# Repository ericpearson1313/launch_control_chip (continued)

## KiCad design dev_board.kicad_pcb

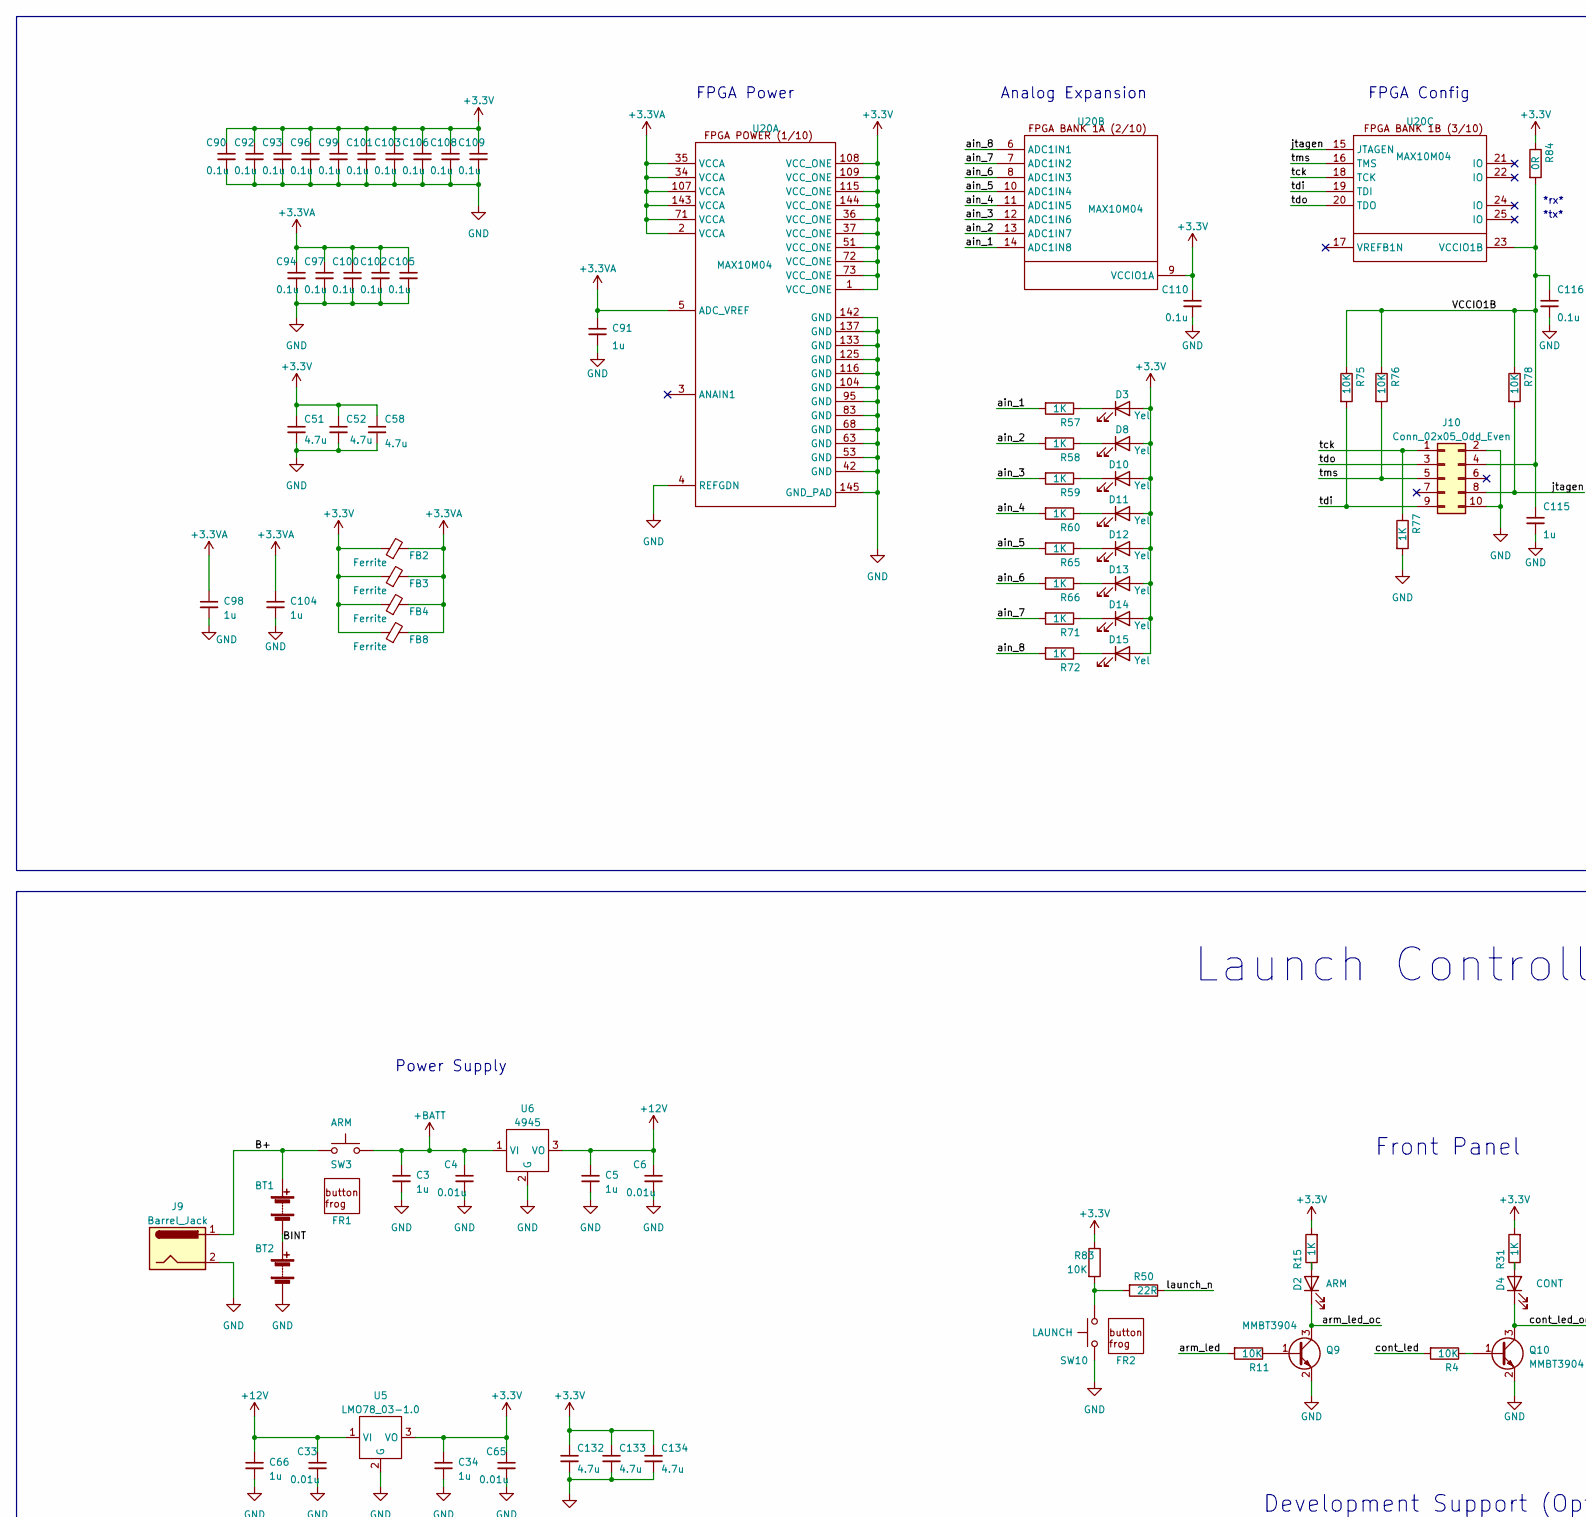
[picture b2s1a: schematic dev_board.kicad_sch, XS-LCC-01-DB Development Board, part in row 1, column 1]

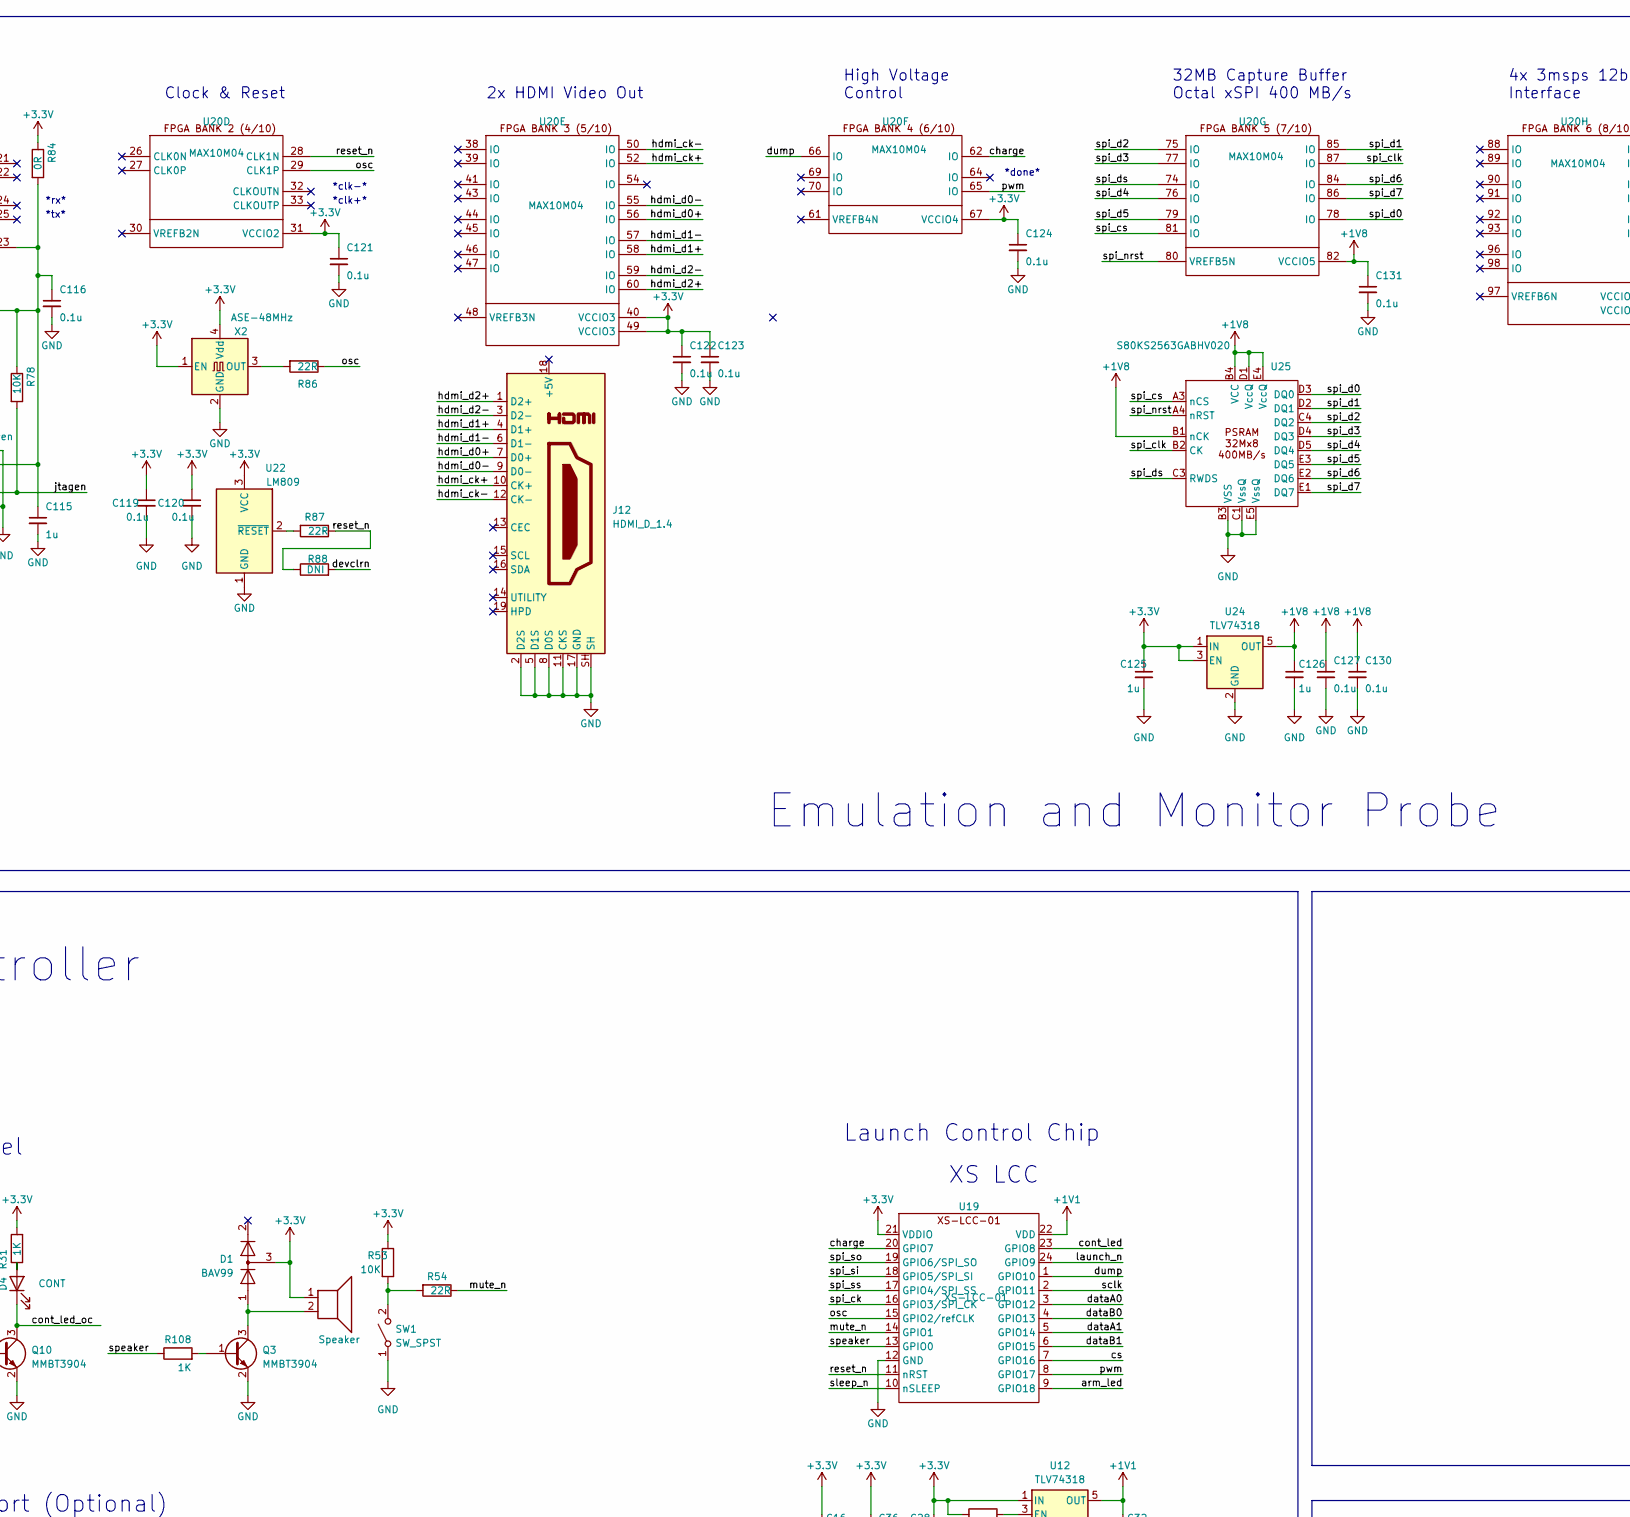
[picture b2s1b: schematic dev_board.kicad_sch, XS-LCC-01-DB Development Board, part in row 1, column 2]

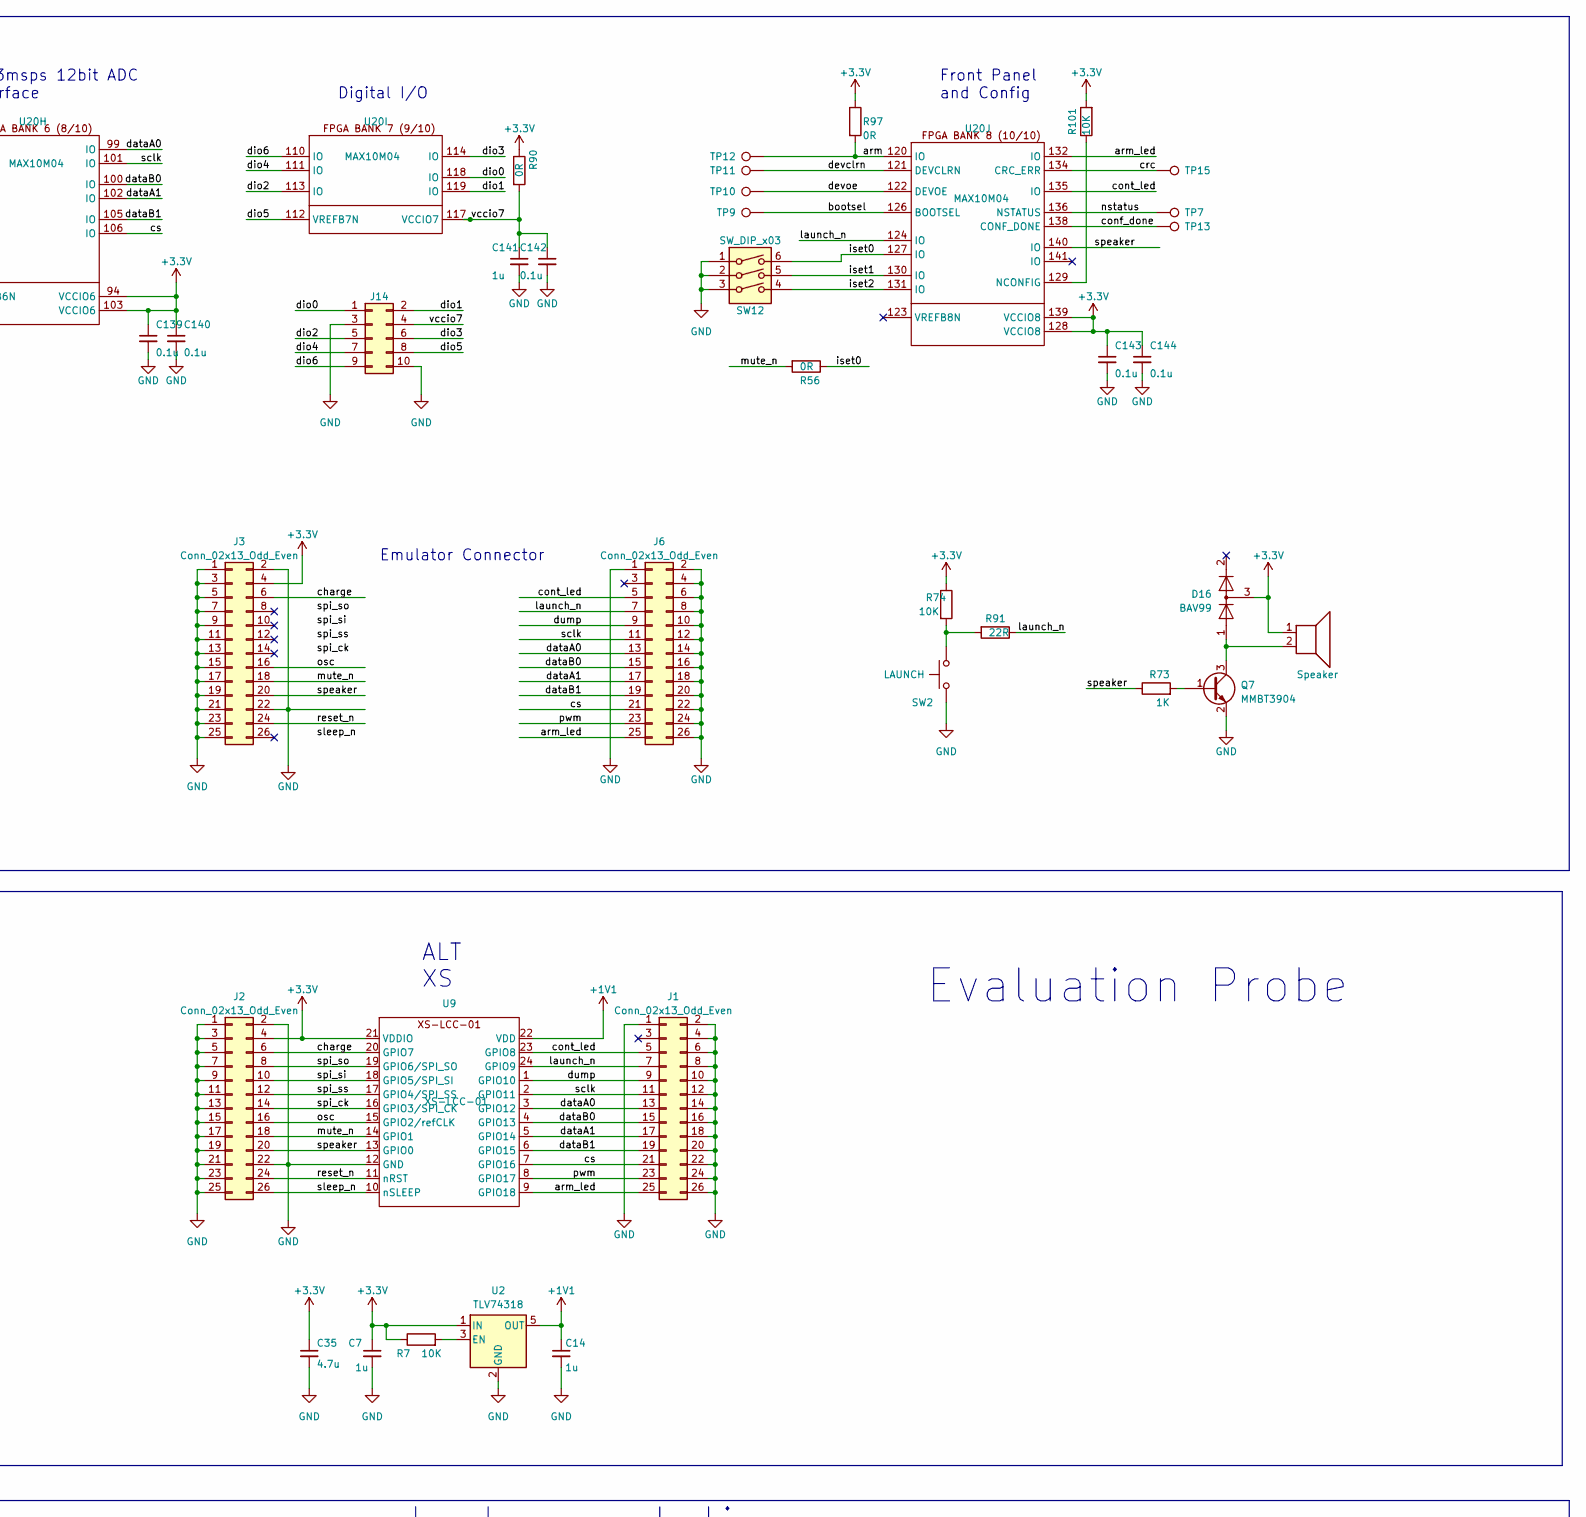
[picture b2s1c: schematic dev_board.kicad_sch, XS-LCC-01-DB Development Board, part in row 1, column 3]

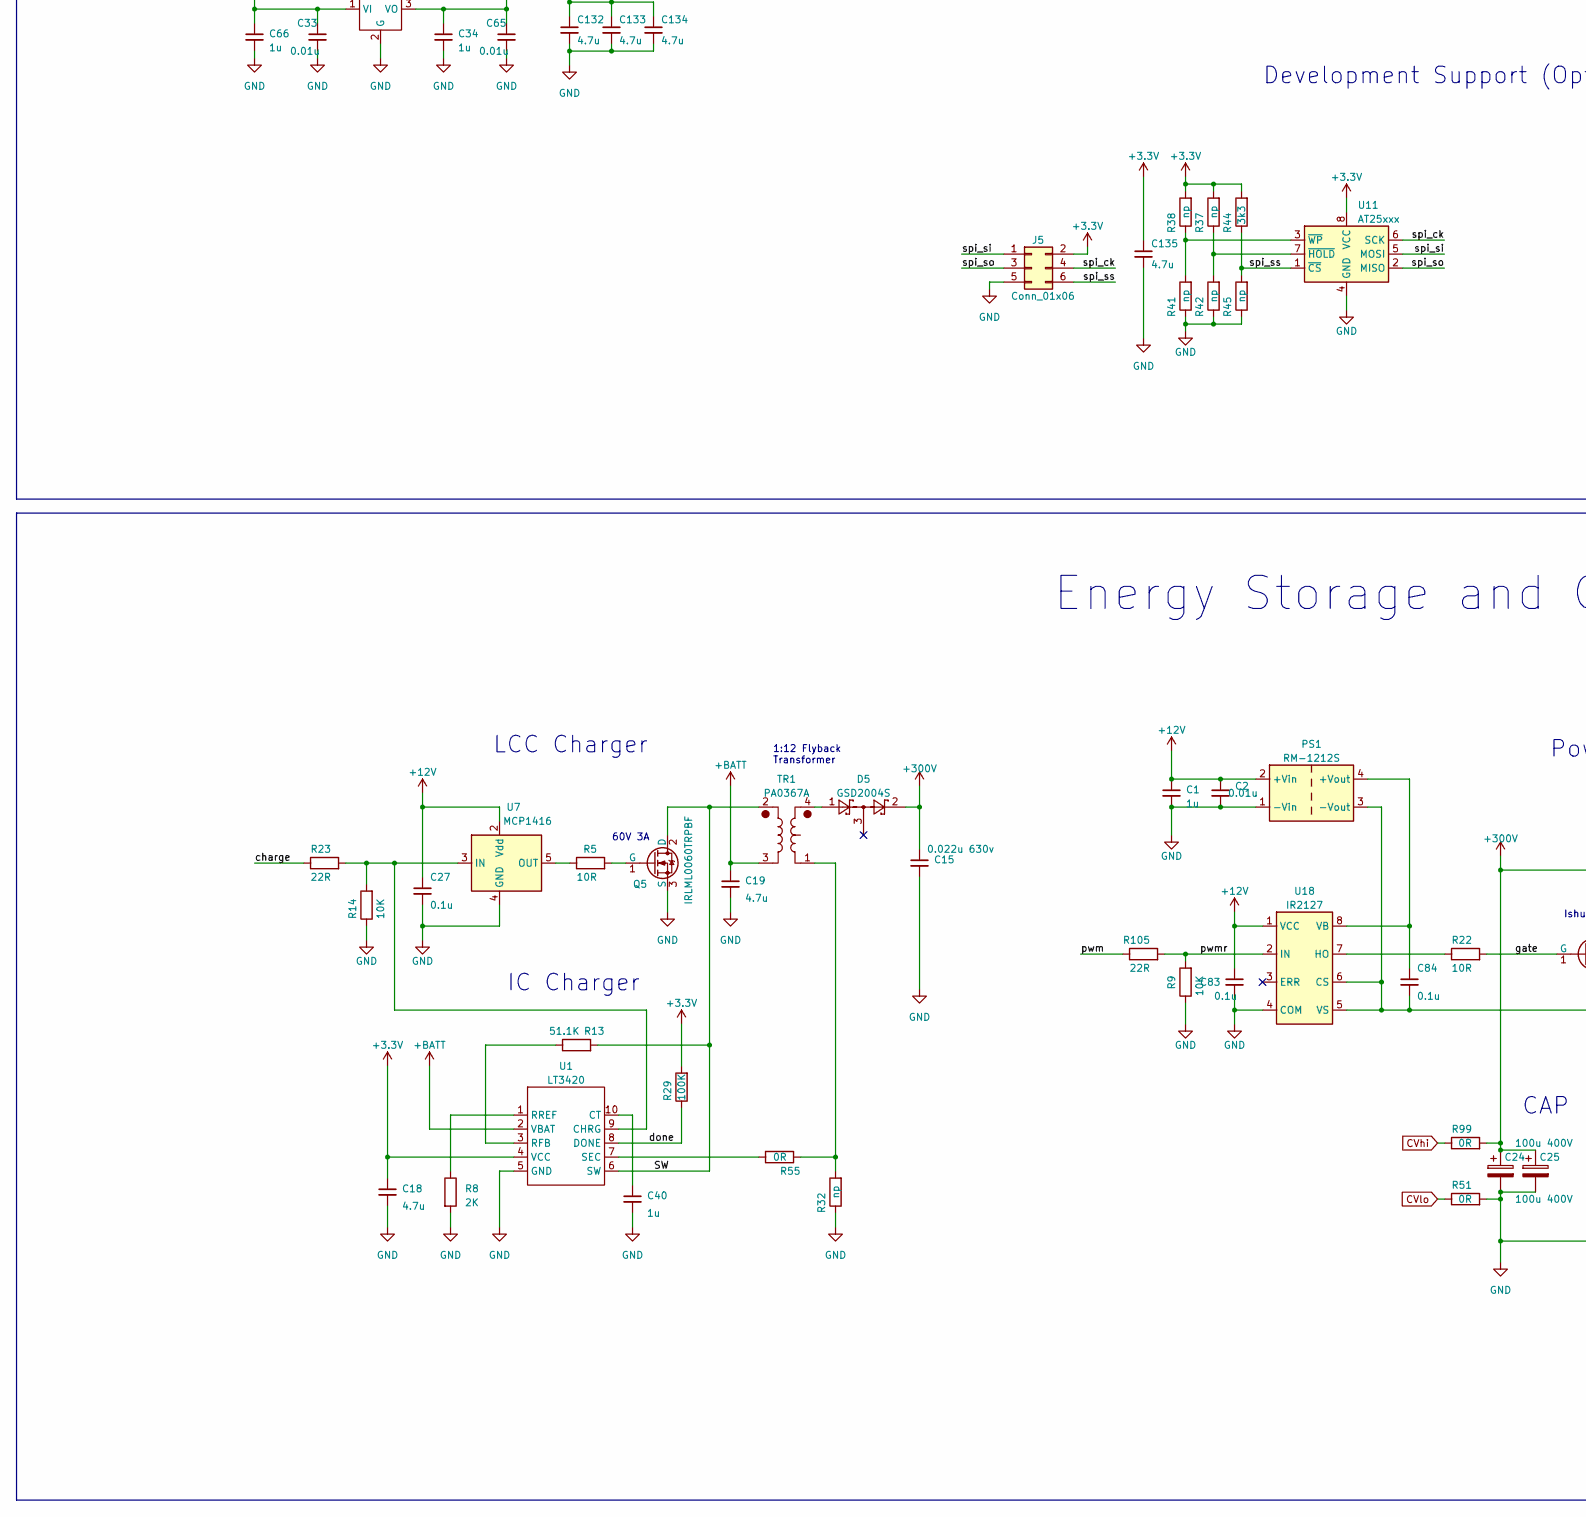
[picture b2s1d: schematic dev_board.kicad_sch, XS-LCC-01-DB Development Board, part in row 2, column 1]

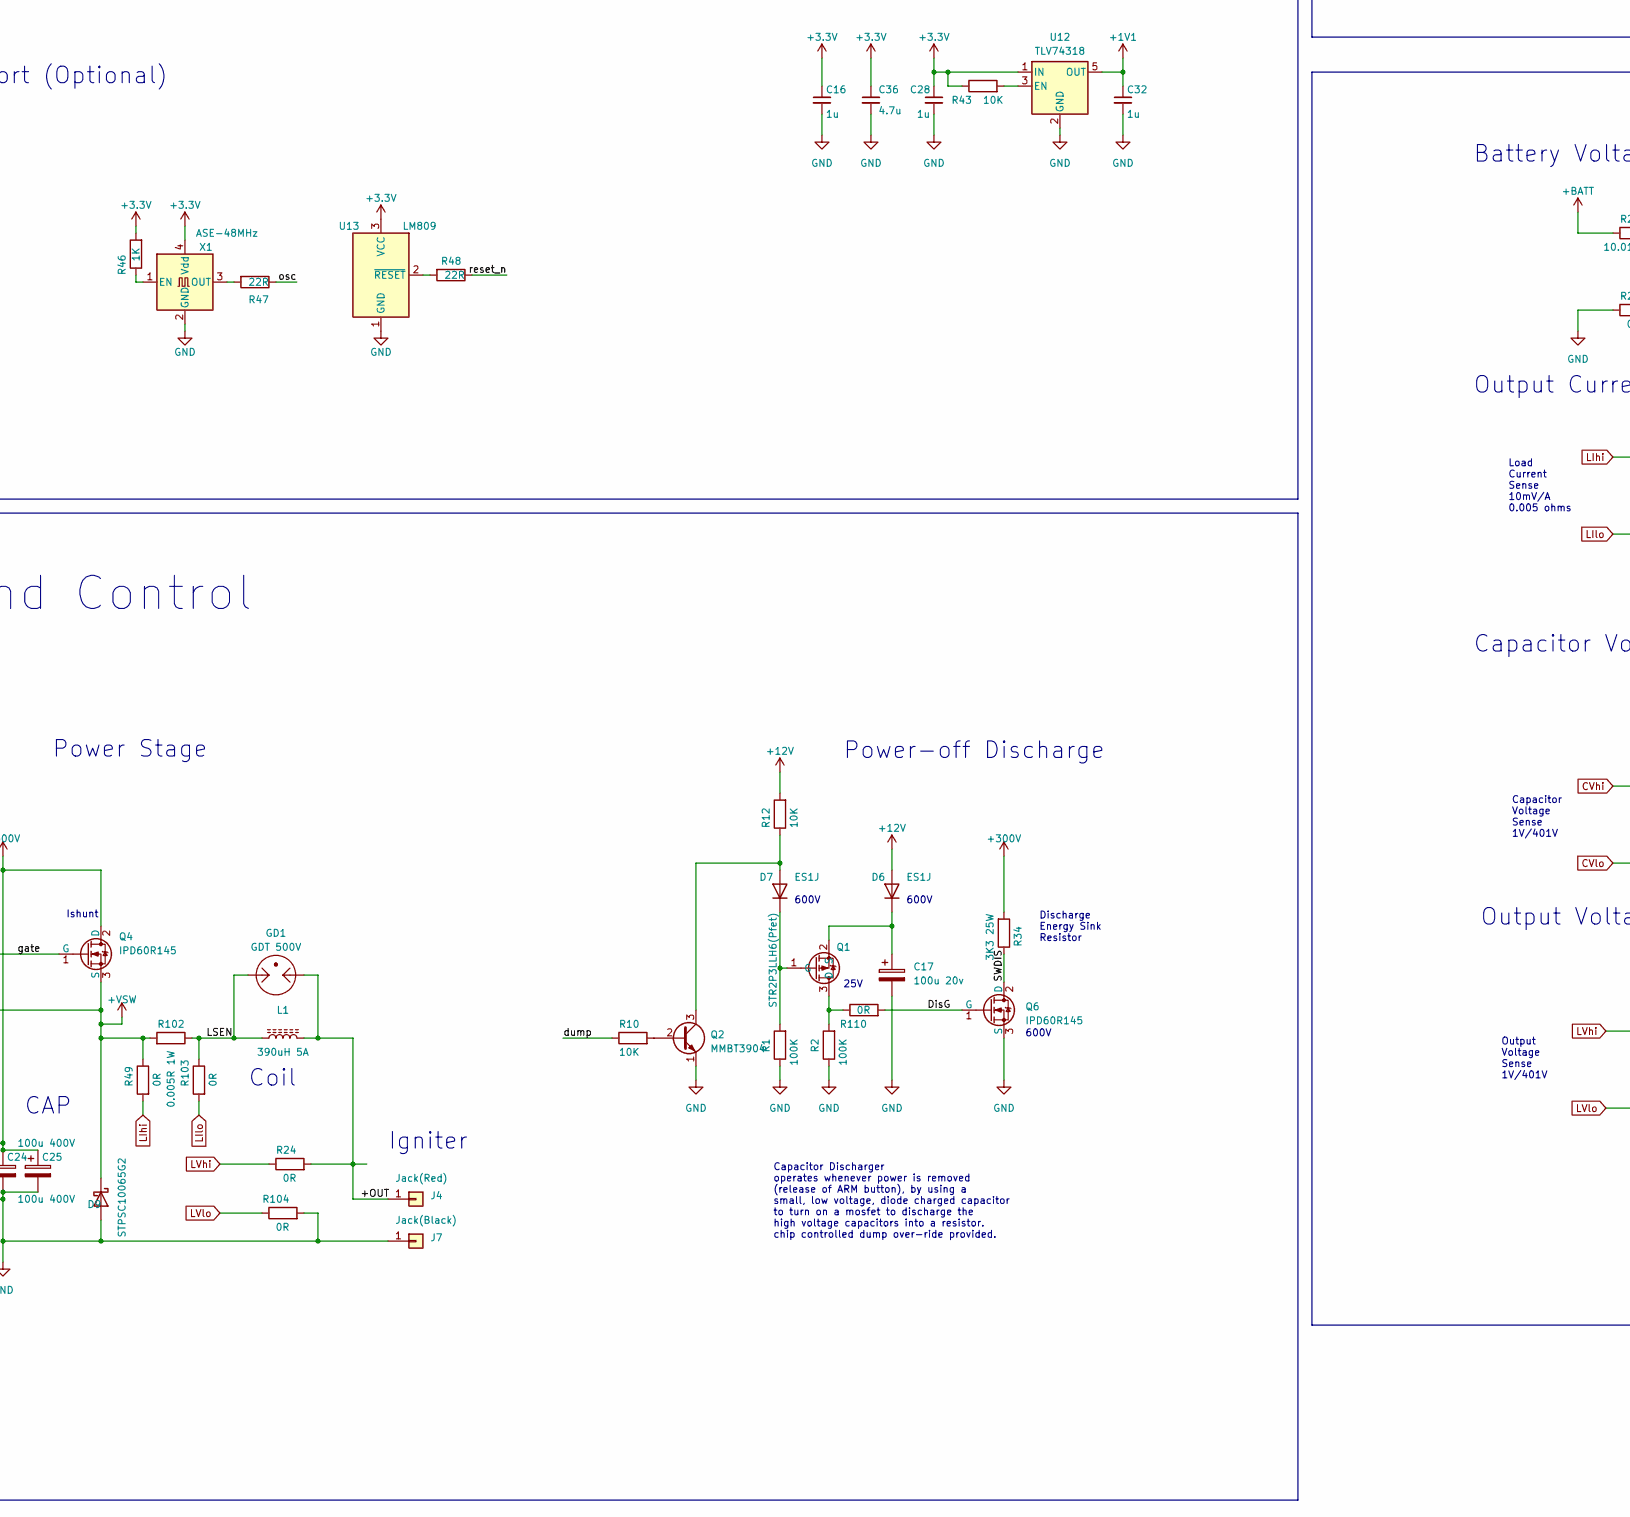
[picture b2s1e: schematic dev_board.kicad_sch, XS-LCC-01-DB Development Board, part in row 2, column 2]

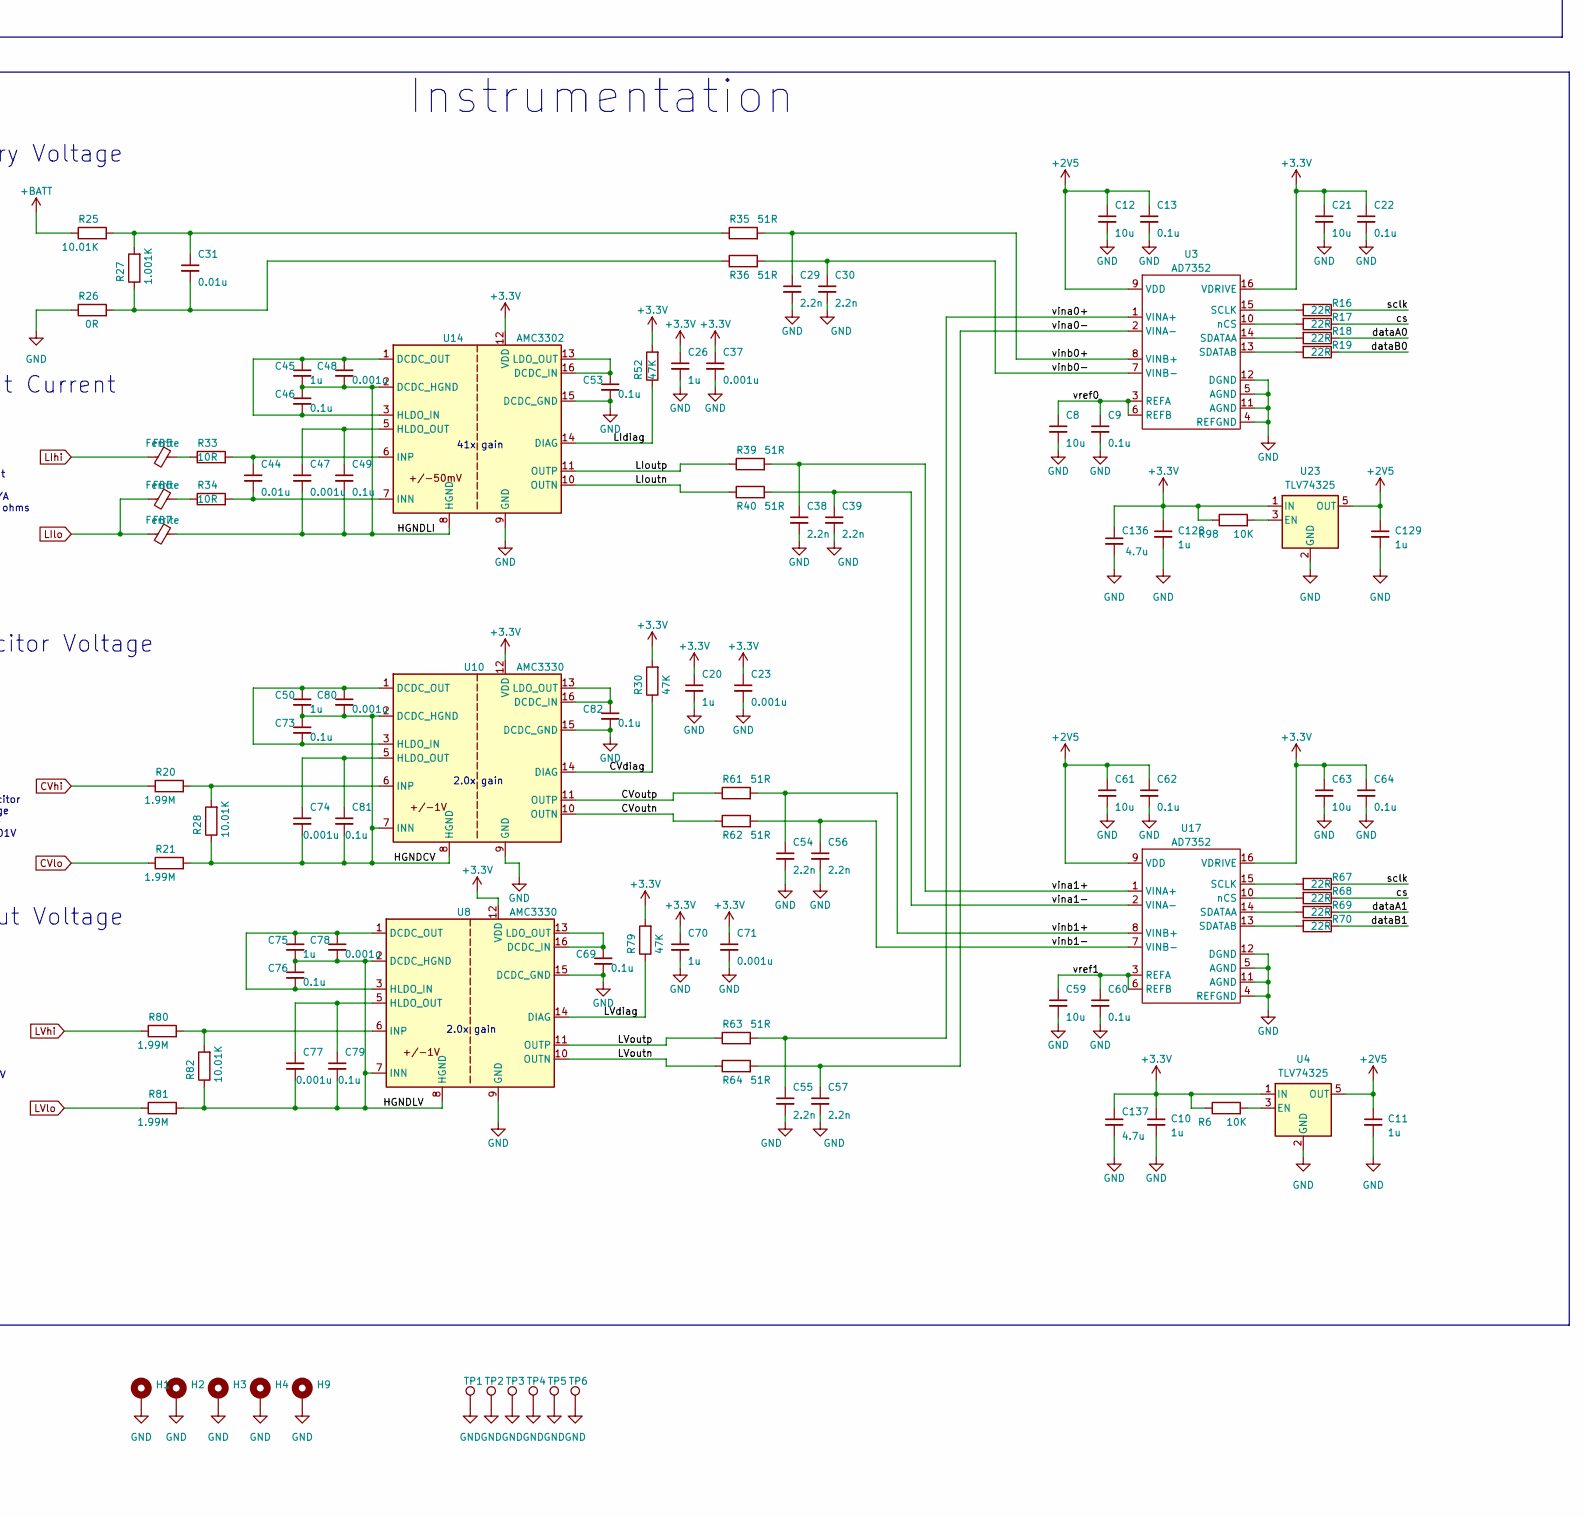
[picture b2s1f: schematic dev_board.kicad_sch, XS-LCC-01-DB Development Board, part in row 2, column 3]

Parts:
BT1, BT2: BatteryHolder_Keystone_2462_2xAA
C1, C3, C5, C7, C10, C11, C14, C16, C20, C26, C28, C32, C34, C40, C45, C50, C66, C70, C75, C91, C98, C104, C115, C125, C126, C128, C129, C141: 1u; C_0603_1608Metric
C2, C4, C6, C31, C33, C44, C65: 0.01u; C_0603_1608Metric
C8, C12, C21, C59, C61, C63: 10u; C_1206_3216Metric
C9, C13, C22, C27, C46, C49, C53, C60, C62, C64, C69, C73, C76, C79, C81, C82, C83, C84, C90, C92, C93, C94, C96, C97, C99, C100, C101, C102, C103, C105, C106, C108, C109, C110, C116, C119, C120, C121, C122, C123, C124, C127, C130, C131, C139, C140, C142, C143, C144: 0.1u; C_0603_1608Metric
C15: 0.022u 630v; C_1206_3216Metric
C17: 100u 20v; C_Radial_D5.0mm_H7.0mm_P2.00mm
C18, C19, C35, C36, C51, C52, C58, C132, C133, C134, C135, C136, C137: 4.7u; C_1206_3216Metric
C23, C37, C47, C48, C71, C74, C77, C78, C80: 0.001u; C_0603_1608Metric
C24, C25: 100u 400V; CP_Radial_D16.0mm_P7.50mm
C29, C30, C38, C39, C54, C55, C56, C57: 2.2n; C_0603_1608Metric
D1, D16: BAV99; SOT-23
D2: ARM; LED_0603_1608Metric
D3, D8, D10, D11, D12, D13, D14, D15: Yel; LED_0603_1608Metric
D4: CONT; LED_0603_1608Metric
D5: GSD2004S; SOT-23; JLC C85606
D6, D7: ES1J; D_SMA; JLC C99410
D9: ‎STPSC10065G2; TO-263-2_TabPin1; JLC C602663
FB2, FB3, FB4, FB5, FB6, FB7, FB8: Ferrite; L_0603_1608Metric
FR1, FR2: button_frog
GD1: GDT 500V; C_1812_4532Metric_Pad1.57x3.40mm_HandSolder
H1, H2, H3, H4, H9: MountingHole_3mm_Pad
J1, J2, J3, J6: Conn_02x13_Odd_Even; PinSocket_2x13_P2.54mm_Vertical
J4: Jack(Red); CalTest_CT3151
J5: Conn_01x06; PinHeader_2x03_P2.54mm_Vertical
J7: Jack(Black); CalTest_CT3151
J9: Barrel_Jack; BarrelJack_CUI_PJ-063AH_Horizontal
J10, J14: Conn_02x05_Odd_Even; PinHeader_2x05_P2.54mm_Vertical
J12: HDMI_D_1.4; HDMI_A_Amphenol_10029449-x01xLF_Horizontal
L1: 390uH 5A; L_Toroid_Vertical_L35.6mm_W17.8mm_P12.70mm_Pulse_E
LS1, LS2: Speaker; PUIAudio_SMT_0825_S_4_R
PS1: RM-1212S; Converter_DCDC_Murata_MEE1SxxxxSC_THT
Q1: STR2P3LLH6(Pfet); SOT-23
Q2, Q3, Q7, Q9, Q10: MMBT3904; SOT-23
Q4, Q6: IPD60R145; TO-252-2; JLC C3277918
Q5: IRLML0060TRPBF; SOT-23; JLC C3277918
R1, R2, R29: 100K; R_0603_1608Metric; JLC C319967
R4, R11, R75, R76, R78, R101: 10K; R_0603_1608Metric; JLC C319967
R5, R22, R33, R34: 10R; R_0603_1608Metric; JLC C778416
R6, R7, R43, R98: 10K; R_0603_1608Metric; JLC C778416
R8: 2K; R_0603_1608Metric; JLC C319700
R9, R12, R14, R53, R74, R83: 10K; R_0603_1608Metric; JLC C491211
R10: 10K; R_0603_1608Metric
R13: 51.1K; R_0603_1608Metric; JLC C234563
R15, R31, R46, R57, R58, R59, R60, R65, R66, R71, R72, R73, R77, R108: 1K; R_0603_1608Metric; JLC C319967
R16, R17, R18, R19, R47, R48, R50, R54, R67, R68, R69, R70, R86, R87, R91: 22R; R_0603_1608Metric; JLC C319967
R20, R21, R80, R81: 1.99M; R_0603_1608Metric; JLC C778416
R23, R105: 22R; R_0603_1608Metric; JLC C778416
R24, R26, R49, R51, R56, R99, R103, R104: 0R; R_0603_1608Metric; JLC C778416
R25, R28, R82: 10.01K; R_0603_1608Metric; JLC C778416
R27: 1.001K; R_0603_1608Metric; JLC C778416
R30, R52, R79: 47K; R_0603_1608Metric; JLC C778416
R32, R37, R38, R41, R42, R45: np; R_0603_1608Metric
R35, R36, R39, R40, R61, R62, R63, R64: 51R; R_0603_1608Metric; JLC C778416
R44: 3k3; R_0603_1608Metric; JLC C319967
R55, R84, R90, R110: 0R; R_0603_1608Metric; JLC C319967
R88: DNI; R_0603_1608Metric; JLC C491211
R97: 0R; R_0603_1608Metric; JLC C491211
R102: 0.005R 1W; R_2818 current sense
SW1: SW_SPST; SW_E-Switch_EG1224_SPDT_Angled
SW2, SW10: LAUNCH; SW_SPST_HP03
SW3: ARM; SW_SPST_HP03
SW12: SW_DIP_x03; SW_DIP_SPSTx03_Slide_Omron_A6S-310x_W8.9mm_P2.54mm
TP1, TP2, TP3, TP4, TP5, TP6: TestPoint_Keystone_5000-5004_Miniature
TP7, TP13: TestPoint_Pad_D1.0mm
TP9, TP10, TP11, TP12, TP15: TestPoint_Pad_D1.5mm
TR1: PA0367A; PA0637A Pulse Coil 3D; JLC C5382098
U1: LT3420; MSOP-10_3x3mm_P0.5mm; JLC C670531
U2, U12, U24: TLV74318; SOT-23-5
U3, U17: AD7352; TSSOP-16_4.4x5mm_P0.65mm
U4, U23: TLV74325; SOT-23-5
U5: LMO78_03-1.0; Converter_DCDC_Murata_OKI-78SR_Horizontal
U6: 4945; Converter_DCDC_Murata_OKI-78SR_Horizontal
U7: MCP1416; SOT-23-5
U8, U10: AMC3330; SOIC-16W_7.5x10.3mm_P1.27mm
U9, U19: XS-LCC-01; QFN-24-3x3mm
U11: AT25xxx; SOIC-8_3.9x4.9mm_P1.27mm
U13, U22: LM809; SOT-23
U14: AMC3302; SOIC-16W_7.5x10.3mm_P1.27mm
U18: IR2127; SOIC-8_3.9x4.9mm_P1.27mm; JLC C356723
U20: MAX10M04; EQFP-144-1EP_20x20mm_P0.5mm_EP8.93x8.7mm_ThermalVias
U25: S80KS2563GABHV020; FBGA-24_6mmx8mm_Layout5x5_P1.00mm
X1, X2: ASE-48MHz; Oscillator_SMD_Abracon_ASV-4Pin_7.0x5.1mm_HandSoldering

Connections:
+1V1: C14.1, C32.1, U2.5 (OUT), U9.22 (VDD), U12.5 (OUT), U19.22 (VDD)
+1V8: C126.1, C127.1, C130.1, C131.1, U20.82 (VCCIO5), U24.5 (OUT), U25.B1 (nCK), U25.B4 (VCC), U25.D1 (VccQ), U25.E4 (VccQ)
+2V5: C11.1, C12.1, C13.1, C61.1, C62.1, C129.1, U3.9 (VDD), U4.5 (OUT), U17.9 (VDD), U23.5 (OUT)
+3.3V: C7.1, C10.1, C16.1, C18.1, C20.1, C21.1, C22.1, C23.1, C26.1, C28.1, C34.1, C35.1, C36.1, C37.1, C51.1, C52.1, C58.1, C63.1, C64.1, C65.1, C70.1, C71.1, C90.1, C92.1, C93.1, C96.1, C99.1, C101.1, C103.1, C106.1, C108.1, C109.1, C110.1, C119.1, C120.1, C121.1, C122.1, C123.1, C124.1, C125.1, C128.1, C132.1, C133.1, C134.1, C135.1, C136.1, C137.1, C139.1, C140.1, C143.1, C144.1, D1.3 (K), D3.2 (A), D8.2 (A), D10.2 (A), D11.2 (A), D12.2 (A), D13.2 (A), D14.2 (A), D15.2 (A), D16.3 (K), FB2.1, FB3.1, FB4.1, FB8.1, J2.4, J3.4, J5.2, LS1.1, LS2.1, R6.1, R7.1, R15.2, R29.2, R30.2, R31.2, R37.2, R38.2, R43.1, R44.2, R46.2, R52.2, R53.1, R74.1, R79.2, R83.1, R84.1, R90.1, R97.1, R98.1, R101.2, U1.4 (VCC), U2.1 (IN), U3.16 (VDRIVE), U4.1 (IN), U5.3 (VO), U8.12 (VDD), U9.21 (VDDIO), U10.12 (VDD), U11.8 (VCC), U12.1 (IN), U13.3 (VCC), U14.12 (VDD), U17.16 (VDRIVE), U19.21 (VDDIO), U20.1 (VCC_ONE), U20.9 (VCCIO1A), U20.31 (VCCIO2), U20.36 (VCC_ONE), U20.37 (VCC_ONE), U20.40 (VCCIO3), U20.49 (VCCIO3), U20.51 (VCC_ONE), U20.67 (VCCIO4), U20.72 (VCC_ONE), U20.73 (VCC_ONE), U20.94 (VCCIO6), U20.103 (VCCIO6), U20.108 (VCC_ONE), U20.109 (VCC_ONE), U20.115 (VCC_ONE), U20.128 (VCCIO8), U20.139 (VCCIO8), U20.144 (VCC_ONE), U22.3 (VCC), U23.1 (IN), U24.1 (IN), U24.3 (EN), X1.4 (Vdd), X2.1 (EN), X2.4 (Vdd)
+3.3VA: C91.1, C94.1, C97.1, C98.1, C100.1, C102.1, C104.1, C105.1, FB2.2, FB3.2, FB4.2, FB8.2, U20.2 (VCCA), U20.5 (ADC_VREF), U20.34 (VCCA), U20.35 (VCCA), U20.71 (VCCA), U20.107 (VCCA), U20.143 (VCCA)
+12V: C1.1, C2.1, C5.1, C6.1, C27.1, C33.1, C66.1, C83.1, D6.2 (A), PS1.2 (+Vin), R12.2, U5.1 (VI), U6.3 (VO), U7.2 (Vdd), U18.1 (VCC)
+BATT: C3.1, C4.1, C19.1, R25.1, SW3.2, TR1.3, U1.2 (VBAT), U6.1 (VI)
+VSW: C84.2, D9.1 (K), PS1.3 (-Vout), Q4.3 (S), R49.1, R102.2, U18.5 (VS), U18.6 (CS)
/+OUT: GD1.1, J4.1, L1.2, R24.2
/B+: BT1.1 (+), J9.1, SW3.1
/BINT: BT1.2 (-), BT2.1 (+)
/CVdiag: R30.1, U10.14 (DIAG)
/CVoutn: R62.1, U10.10 (OUTN)
/CVoutp: R61.1, U10.11 (OUTP)
/DisG: Q6.1 (G), R110.2
/HGNDCV: C50.2, C73.1, C74.2, C80.2, C81.2, R21.2, R28.1, U10.2 (DCDC_HGND), U10.7 (INN), U10.8 (HGND)
/HGNDLI: C45.2, C46.1, C47.2, C48.2, C49.2, FB7.1, U14.2 (DCDC_HGND), U14.8 (HGND)
/HGNDLV: C75.2, C76.1, C77.2, C78.2, C79.2, R81.2, R82.1, U8.2 (DCDC_HGND), U8.7 (INN), U8.8 (HGND)
/LIdiag: R52.1, U14.14 (DIAG)
/LIoutn: R40.1, U14.10 (OUTN)
/LIoutp: R39.1, U14.11 (OUTP)
/LSEN: GD1.3, L1.1, R102.1, R103.1
/LVdiag: R79.1, U8.14 (DIAG)
/LVoutn: R64.1, U8.10 (OUTN)
/LVoutp: R63.1, U8.11 (OUTP)
/SW: Q5.2 (D), R13.2, TR1.2, U1.6 (SW)
/VCCIO1B: C115.1, C116.1, J10.4, R75.1, R76.1, R78.1, R84.2, U20.23 (VCCIO1B)
/ain_1: R57.2, U20.14 (ADC1IN8)
/ain_2: R58.2, U20.13 (ADC1IN7)
/ain_3: R59.2, U20.12 (ADC1IN6)
/ain_4: R60.2, U20.11 (ADC1IN5)
/ain_5: R65.2, U20.10 (ADC1IN4)
/ain_6: R66.2, U20.8 (ADC1IN3)
/ain_7: R71.2, U20.7 (ADC1IN2)
/ain_8: R72.2, U20.6 (ADC1IN1)
/arm: R97.2, TP12.1, U20.120 (IO)
/arm_led: J1.25, J6.25, R11.2, U9.9 (GPIO18), U19.9 (GPIO18), U20.132 (IO)
/arm_led_oc: D2.1 (K), Q9.3 (C)
/bootsel: TP9.1, U20.126 (BOOTSEL)
/charge: J2.6, J3.6, R23.1, U9.20 (GPIO7), U19.20 (GPIO7), U20.62 (IO)
/conf_done: TP13.1, U20.138 (CONF_DONE)
/cont_led: J1.5, J6.5, R4.2, U9.23 (GPIO8), U19.23 (GPIO8), U20.135 (IO)
/cont_led_oc: D4.1 (K), Q10.3 (C)
/crc: TP15.1, U20.134 (CRC_ERR)
/cs: J1.21, J6.21, R17.1, R68.1, U9.7 (GPIO16), U19.7 (GPIO16), U20.106 (IO)
/dataA0: J1.13, J6.13, R18.1, U9.3 (GPIO12), U19.3 (GPIO12), U20.99 (IO)
/dataA1: J1.17, J6.17, R69.1, U9.5 (GPIO14), U19.5 (GPIO14), U20.102 (IO)
/dataB0: J1.15, J6.15, R19.1, U9.4 (GPIO13), U19.4 (GPIO13), U20.100 (IO)
/dataB1: J1.19, J6.19, R70.1, U9.6 (GPIO15), U19.6 (GPIO15), U20.105 (IO)
/devclrn: R88.2, TP11.1, U20.121 (DEVCLRN)
/devoe: TP10.1, U20.122 (DEVOE)
/dio0: J14.1, U20.118 (IO)
/dio1: J14.2, U20.119 (IO)
/dio2: J14.5, U20.113 (IO)
/dio3: J14.6, U20.114 (IO)
/dio4: J14.7, U20.111 (IO)
/dio5: J14.8, U20.112 (VREFB7N)
/dio6: J14.9, U20.110 (IO)
/done: R29.1, U1.8 (DONE)
/dump: J1.9, J6.9, R10.1, U9.1 (GPIO10), U19.1 (GPIO10), U20.66 (IO)
/gate: Q4.1 (G), R22.2
/hdmi_ck+: J12.10 (CK+), U20.52 (IO)
/hdmi_ck-: J12.12 (CK-), U20.50 (IO)
/hdmi_d0+: J12.7 (D0+), U20.56 (IO)
/hdmi_d0-: J12.9 (D0-), U20.55 (IO)
/hdmi_d1+: J12.4 (D1+), U20.58 (IO)
/hdmi_d1-: J12.6 (D1-), U20.57 (IO)
/hdmi_d2+: J12.1 (D2+), U20.60 (IO)
/hdmi_d2-: J12.3 (D2-), U20.59 (IO)
/iset0: R56.1, SW12.6, U20.127 (IO)
/iset1: SW12.5, U20.130 (IO)
/iset2: SW12.4, U20.131 (IO)
/jtagen: J10.8, R78.2, U20.15 (JTAGEN)
/launch_n: J1.7, J6.7, R50.1, R91.1, U9.24 (GPIO9), U19.24 (GPIO9), U20.124 (IO)
/mute_n: J2.18, J3.18, R54.1, R56.2, U9.14 (GPIO1), U19.14 (GPIO1)
/nstatus: TP7.1, U20.136 (NSTATUS)
/osc: J2.16, J3.16, R47.1, R86.1, U9.15 (GPIO2/refCLK), U19.15 (GPIO2/refCLK), U20.29 (CLK1P)
/pwm: J1.23, J6.23, R105.1, U9.8 (GPIO17), U19.8 (GPIO17), U20.65 (IO)
/pwmr: R9.2, R105.2, U18.2 (IN)
/reset_n: J2.24, J3.24, R48.1, R87.1, R88.1, U9.11 (nRST), U19.11 (nRST), U20.28 (CLK1N)
/sclk: J1.11, J6.11, R16.1, R67.1, U9.2 (GPIO11), U19.2 (GPIO11), U20.101 (IO)
/sleep_n: J2.26, U9.10 (nSLEEP), U19.10 (nSLEEP)
/speaker: J2.20, J3.20, R73.1, R108.1, U9.13 (GPIO0), U19.13 (GPIO0), U20.140 (IO)
/spi_ck: J2.14, J5.4, U9.16 (GPIO3/SPI_CK), U11.6 (SCK), U19.16 (GPIO3/SPI_CK)
/spi_clk: U20.87 (IO), U25.B2 (CK)
/spi_cs: U20.81 (IO), U25.A3 (nCS)
/spi_d0: U20.78 (IO), U25.D3 (DQ0)
/spi_d1: U20.85 (IO), U25.D2 (DQ1)
/spi_d2: U20.75 (IO), U25.C4 (DQ2)
/spi_d3: U20.77 (IO), U25.D4 (DQ3)
/spi_d4: U20.76 (IO), U25.D5 (DQ4)
/spi_d5: U20.79 (IO), U25.E3 (DQ5)
/spi_d6: U20.84 (IO), U25.E2 (DQ6)
/spi_d7: U20.86 (IO), U25.E1 (DQ7)
/spi_ds: U20.74 (IO), U25.C3 (RWDS)
/spi_nrst: U20.80 (VREFB5N), U25.A4 (nRST)
/spi_si: J2.10, J5.1, U9.18 (GPIO5/SPI_SI), U11.5 (MOSI), U19.18 (GPIO5/SPI_SI)
/spi_so: J2.8, J5.3, U9.19 (GPIO6/SPI_SO), U11.2 (MISO), U19.19 (GPIO6/SPI_SO)
/spi_ss: J2.12, J5.6, R44.1, R45.2, U9.17 (GPIO4/SPI_SS), U11.1 (~CS), U19.17 (GPIO4/SPI_SS)
/tck: J10.1, R77.1, U20.18 (TCK)
/tdi: J10.9, R75.2, U20.19 (TDI)
/tdo: J10.3, U20.20 (TDO)
/tms: J10.5, R76.2, U20.16 (TMS)
/vccio7: C141.1, C142.1, J14.4, R90.2, U20.117 (VCCIO7)
/vina0+: C55.1, R63.2, U3.1 (VINA+)
/vina0-: C57.1, R64.2, U3.2 (VINA-)
/vina1+: C38.1, R39.2, U17.1 (VINA+)
/vina1-: C39.1, R40.2, U17.2 (VINA-)
/vinb0+: C29.1, R35.2, U3.8 (VINB+)
/vinb0-: C30.1, R36.2, U3.7 (VINB-)
/vinb1+: C54.1, R61.2, U17.8 (VINB+)
/vinb1-: C56.1, R62.2, U17.7 (VINB-)
/vref0: C8.1, C9.1, U3.3 (REFA), U3.6 (REFB)
/vref1: C59.1, C60.1, U17.3 (REFA), U17.6 (REFB)
CVhi: R20.1, R99.1
CVlo: R21.1, R51.1
GND: BT2.2 (-), C1.2, C2.2, C3.2, C4.2, C5.2, C6.2, C7.2, C8.2, C9.2, C10.2, C11.2, C12.2, C13.2, C14.2, C15.2, C16.2, C17.2, C18.2, C19.2, C20.2, C21.2, C22.2, C23.2, C24.2, C25.2, C26.2, C27.2, C28.2, C29.2, C30.2, C32.2, C33.2, C34.2, C35.2, C36.2, C37.2, C38.2, C39.2, C40.2, C51.2, C52.2, C53.2, C54.2, C55.2, C56.2, C57.2, C58.2, C59.2, C60.2, C61.2, C62.2, C63.2, C64.2, C65.2, C66.2, C69.2, C70.2, C71.2, C82.2, C83.2, C90.2, C91.2, C92.2, C93.2, C94.2, C96.2, C97.2, C98.2, C99.2, C100.2, C101.2, C102.2, C103.2, C104.2, C105.2, C106.2, C108.2, C109.2, C110.2, C115.2, C116.2, C119.2, C120.2, C121.2, C122.2, C123.2, C124.2, C125.2, C126.2, C127.2, C128.2, C129.2, C130.2, C131.2, C132.2, C133.2, C134.2, C135.2, C136.2, C137.2, C139.2, C140.2, C141.2, C142.2, C143.2, C144.2, D9.2 (A), H1.1, H2.1, H3.1, H4.1, H9.1, J1.1, J1.2, J1.4, J1.6, J1.8, J1.10, J1.12, J1.14, J1.16, J1.18, J1.20, J1.22, J1.24, J1.26, J2.1, J2.2, J2.3, J2.5, J2.7, J2.9, J2.11, J2.13, J2.15, J2.17, J2.19, J2.21, J2.22, J2.23, J2.25, J3.1, J3.2, J3.3, J3.5, J3.7, J3.9, J3.11, J3.13, J3.15, J3.17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
LIhi: FB5.2, R49.2
LIlo: FB6.2, FB7.2, R103.2
LVhi: R24.1, R80.1
LVlo: R81.1, R104.1
unnamed: C31.1, R25.2, R27.2, R35.1
unnamed: C31.2, R26.2, R27.1, R36.1
unnamed: D2.2 (A), R15.1
unnamed: D3.1 (K), R57.1
unnamed: D4.2 (A), R31.1
unnamed: D5.1, TR1.4
unnamed: C17.1, D6.1 (K), Q1.2 (S)
unnamed: D7.2 (A), Q2.3 (C), R12.1
unnamed: D7.1 (K), Q1.1 (G), R1.2
unnamed: D8.1 (K), R58.1
unnamed: D10.1 (K), R59.1
unnamed: D11.1 (K), R60.1
unnamed: D12.1 (K), R65.1
unnamed: D13.1 (K), R66.1
unnamed: D14.1 (K), R71.1
unnamed: D15.1 (K), R72.1
unnamed: FB5.1, R33.1
unnamed: C84.1, PS1.4 (+Vout), U18.8 (VB)
unnamed: Q1.3 (D), R2.2, R110.1
unnamed: Q2.2 (B), R10.2
unnamed: Q3.1 (B), R108.2
unnamed: D1.1 (K), LS1.2, Q3.3 (C)
unnamed: Q5.1 (G), R5.2
unnamed: Q7.1 (B), R73.2
unnamed: D16.1 (K), LS2.2, Q7.3 (C)
unnamed: Q9.1 (B), R11.1
unnamed: Q10.1 (B), R4.1
unnamed: R32.2, R55.1, TR1.1
unnamed: R50.2, R83.2, SW10.2
unnamed: R74.2, R91.2, SW2.2
unnamed: R53.2, R54.2, SW1.2 (B)
unnamed: R14.2, R23.2, U1.9 (CHRG), U7.3 (IN)
unnamed: C40.1, U1.10 (CT)
unnamed: R13.1, U1.3 (RFB)
unnamed: R8.1, U1.1 (RREF)
unnamed: R55.2, U1.7 (SEC)
unnamed: R7.2, U2.3 (EN)
unnamed: R16.2, U3.15 (SCLK)
unnamed: R18.2, U3.14 (SDATAA)
unnamed: R19.2, U3.13 (SDATAB)
unnamed: R17.2, U3.10 (nCS)
unnamed: R6.2, U4.3 (EN)
unnamed: R5.1, U7.5 (OUT)
unnamed: C69.1, U8.13 (LDO_OUT), U8.16 (DCDC_IN)
unnamed: C75.1, C76.2, C78.1, U8.1 (DCDC_OUT), U8.3 (HLDO_IN)
unnamed: C77.1, C79.1, U8.5 (HLDO_OUT)
unnamed: R80.2, R82.2, U8.6 (INP)
unnamed: C82.1, U10.13 (LDO_OUT), U10.16 (DCDC_IN)
unnamed: C50.1, C73.2, C80.1, U10.1 (DCDC_OUT), U10.3 (HLDO_IN)
unnamed: C74.1, C81.1, U10.5 (HLDO_OUT)
unnamed: R20.2, R28.2, U10.6 (INP)
unnamed: R37.1, R42.2, U11.7 (~HOLD)
unnamed: R38.1, R41.2, U11.3 (~WP)
unnamed: R43.2, U12.3 (EN)
unnamed: R48.2, U13.2 (~RESET)
unnamed: C53.1, U14.13 (LDO_OUT), U14.16 (DCDC_IN)
unnamed: C45.1, C46.2, C48.1, U14.1 (DCDC_OUT), U14.3 (HLDO_IN)
unnamed: C47.1, C49.1, U14.5 (HLDO_OUT)
unnamed: C44.1, R33.2, U14.6 (INP)
unnamed: R67.2, U17.15 (SCLK)
unnamed: R69.2, U17.14 (SDATAA)
unnamed: R70.2, U17.13 (SDATAB)
unnamed: R68.2, U17.10 (nCS)
unnamed: R22.1, U18.7 (HO)
unnamed: R101.1, U20.129 (NCONFIG)
unnamed: R87.2, U22.2 (~RESET)
unnamed: R98.2, U23.3 (EN)
unnamed: R46.1, X1.1 (EN)
unnamed: R47.2, X1.3 (OUT)
unnamed: R86.2, X2.3 (OUT)

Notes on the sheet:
2x HDMI Video Out
600V
Evaluation Probe
Power-off Discharge
Igniter
Capacitor Voltage
Energy Storage and Control
*done*
41x gain
Coil
Capacitor Voltage Sense 1V/401V
High Voltage Control
Output Voltage
Ishunt
Output Voltage Sense 1V/401V
Instrumentation
CAP
Emulator Connector
32MB Capture Buffer Octal xSPI 400 MB/s
Launch Control Chip
2.0x gain
XS LCC
25V
FPGA Config
Front Panel
IC Charger
4x 3msps 12bit ADC Interface
Development Support (Optional)
ALT XS
Analog Expansion
FPGA Power
Emulation and Monitor Probe
Discharge Energy Sink Resistor
Digital I/O
*clk+*
Clock & Reset
*tx*
60V 3A
Power Supply
*clk-*

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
